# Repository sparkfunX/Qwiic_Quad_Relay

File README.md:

SparkX Qwiic Quad Relay
========================================

->  <-

[*SparkX Qwiic Quad Relay (SPX-15032)*](https://www.sparkfun.com/products/15032)
The Qwiic Quad Relay is a product designed for switching not one, but **four** high powered devices, from your Arduino or other low powered microcontroller using I<sup>2</sup>C. It's rocking four [relays](https://www.sparkfun.com/products/100) on its' PCB rated up to 5 Amps per channel at 250VAC. Each channel is sporting its own colored LED and silk for easy identification, and has screw terminals for easy connection. 

The board is made to integrate easily into the [Qwiic environment](https://www.sparkfun.com/qwiic) with Qwiic connectors on each side for easy daisy chaining. At the heart of the product is an ATtiny84 with its own I<sup>2</sup>C address awaiting for I<sup>2</sup>C commands that are designated to turn on and off individual channels or _all_ the channels at once! All of this is detailed nicely in provided example code, which also walks you through changing the boards single I<sup>2</sup>C address. There is a four pin header broken out for those of you not taking advantage of the Qwiic connector.

The onboard barrel jack is rated for wall warts in the range, 7-15V but there is a jumper on the underside in the case that your wall wart is 5V. Messing with such high voltage can be dangerous! We've included many safety precautions onto the PCB including, wide traces designed for high amperage, ground isolation between the relay and other circuitry, and a milled out area around the common pin of the relay.

Repository Contents
-------------------

* **/Firmware** - Latest firmware and examples. 
* **/Arduino Example** - Examples on how to use the product with buttons and switches, with hardware interrupts and without.
* **/Hardware** - Eagle design files (.brd, .sch)

License Information
-------------------

This product is _**open source**_! 

Please review the LICENSE.md file for license information. 

If you have any questions or concerns on licensing, please contact techsupport@sparkfun.com.

Please use, reuse, and modify these files as you see fit. Please maintain attribution to SparkFun Electronics and release under the same license.

Distributed as-is; no warranty is given.

- Your friends at SparkFun.

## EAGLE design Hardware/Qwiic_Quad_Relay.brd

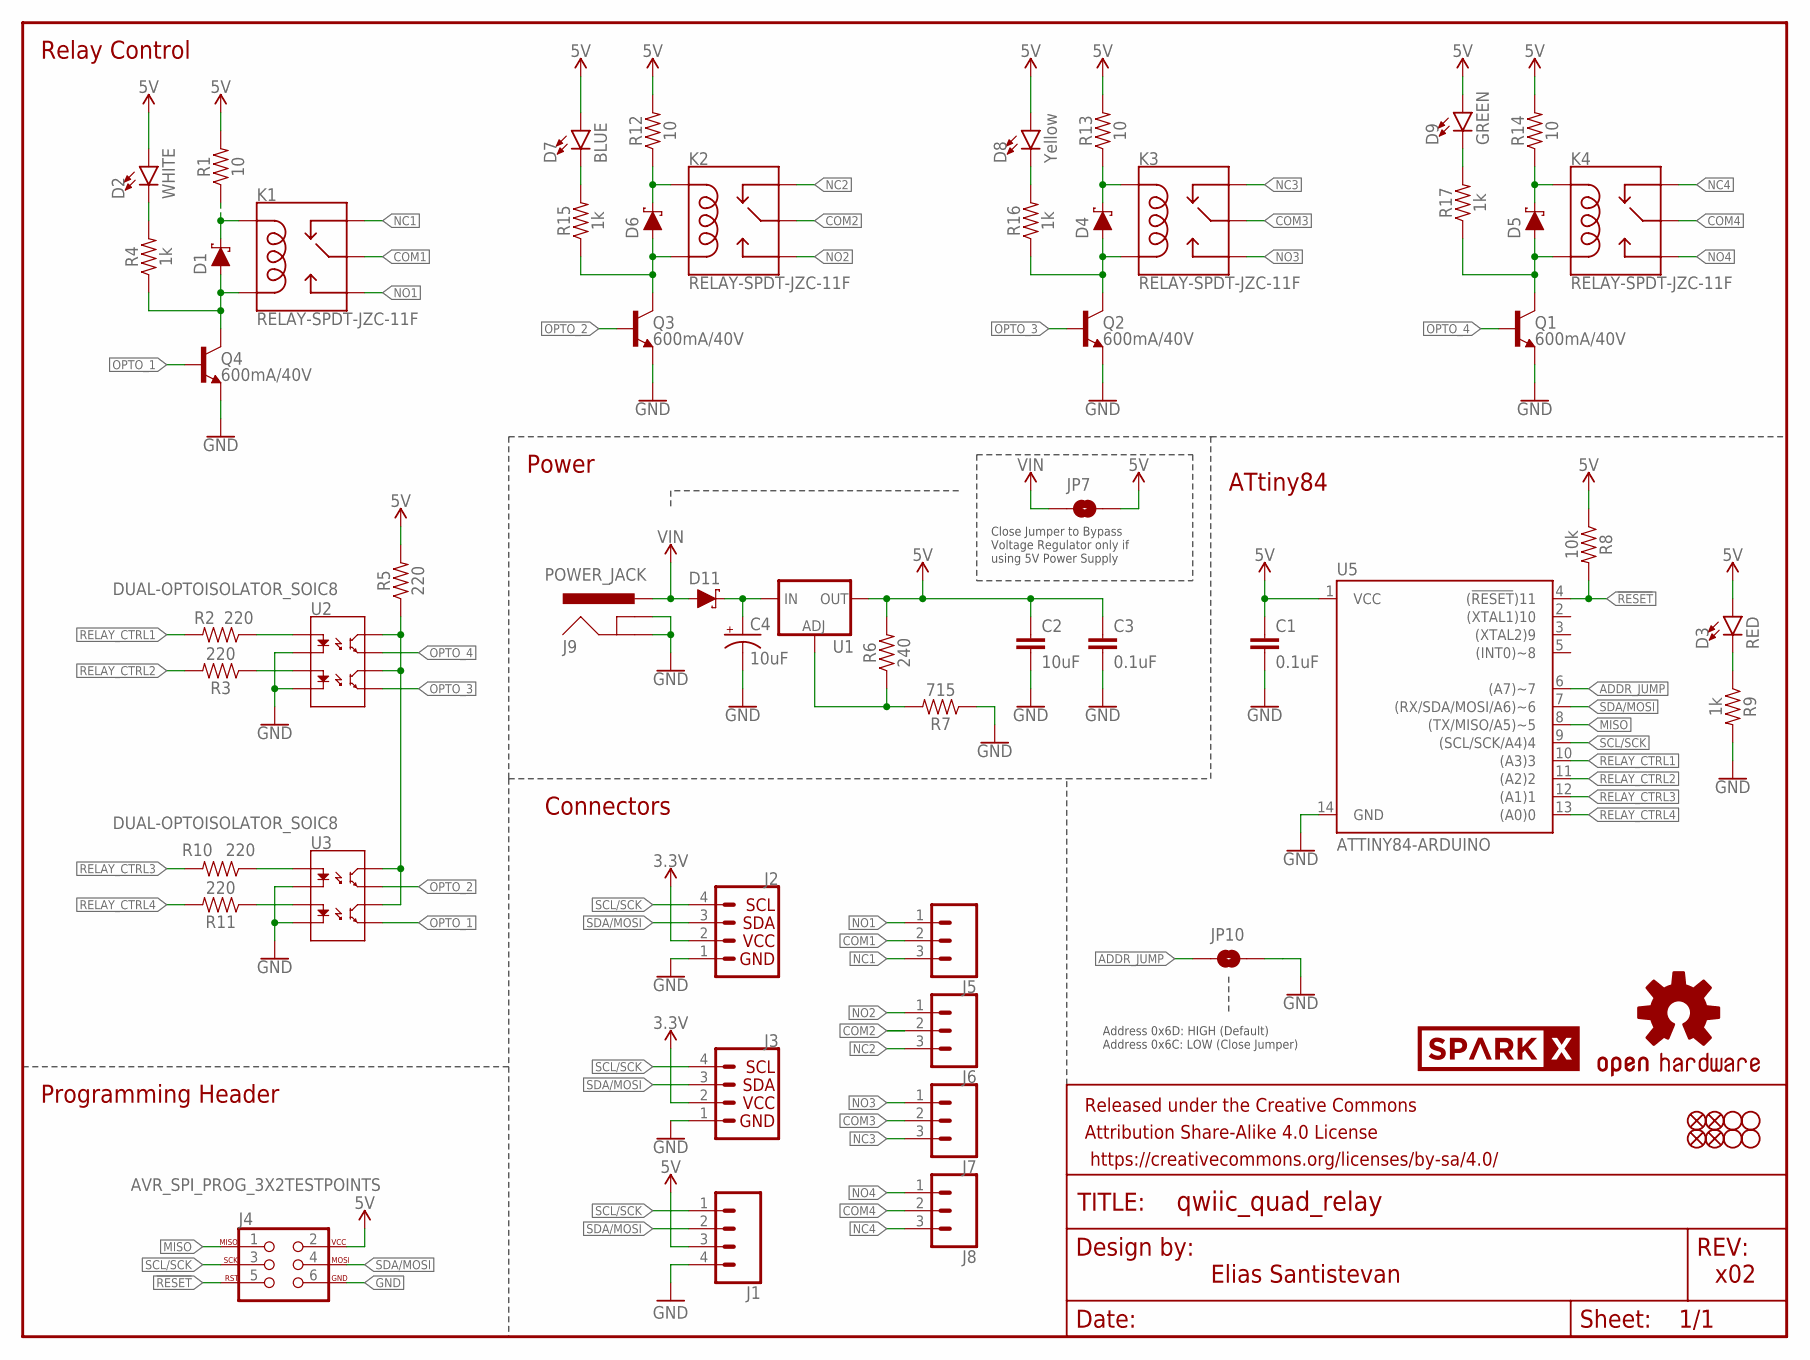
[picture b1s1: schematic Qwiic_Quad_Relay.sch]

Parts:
C1, C3: 0.1uF; 0603
C2: 10uF; 0603
C4: 10uF; EIA3528
D1, D4, D5, D6: 1A/23V/620mV; SOD-323
D2: WHITE; LED-0603
D3: RED; LED-0603
D7: BLUE; LED-0603
D8: Yellow; LED-0603
D9: GREEN; LED-0603
D11: 1A/40V/500mV; SMA-DIODE
FRAME1: FRAME-LETTER; CREATIVE_COMMONS
J1: CONN_041X04_NO_SILK; 1X04_NO_SILK
J2, J3: Qwiic Right Angle; 1X04_1MM_RA
J4: AVR_SPI_PROG_3X2TESTPOINTS; 2X3_TEST_POINTS
J5, J6, J7, J8: CONN_03-SCREW-5MM; SCREWTERMINAL-5MM-3
J9: POWER_JACK; POWER_JACK_PTH
JP1, JP3, JP4, JP5: STAND-OFF
JP2, JP6, JP8, JP9: FIDUCIAL1X2; FIDUCIAL-1X2
JP7, JP10: JUMPER-SMT_2_NO_SILK; SMT-JUMPER_2_NO_SILK
K1, K2, K3, K4: RELAY-SPDT-JZC-11F; RELAY-JZC
LOGO1: OSHW-LOGOS; OSHW-LOGO-S
Q1, Q2, Q3, Q4: 600mA/40V; SOT23-3
R1, R12, R13, R14: 10; 0603
R2, R3, R5, R10, R11: 220; 0603
R4, R9, R15, R16, R17: 1k; 0603
R6: 240; 0603
R7: 715; 0603
R8: 10k; 0603
U1: V_REG_LM1117SOT223; SOT223
U2, U3: DUAL-OPTOISOLATOR_SOIC8; SO08
U5: ATTINY84-ARDUINO; SO14
U$12: SPARKX-LOGO4; SPARKX-MEDIUM

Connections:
3.3V: J2.2, J3.2
5V: C1.1, C2.1, C3.1, D2.A, D3.A, D7.A, D8.A, D9.A, J1.3, J4.2, JP7.2, R1.2, R5.2, R6.2, R8.1, R12.2, R13.2, R14.2, U1.2 (OUT), U1.4 (OUT), U5.1 (VCC)
!RESET: J4.5, R8.2, U5.4 ((!RESET!)11)
ADDR_JUMP: JP10.1, U5.6 ((A7)~7)
COM1: J5.2, K1.4 (MAIN)
COM2: J6.2, K2.4 (MAIN)
COM3: J7.2, K3.4 (MAIN)
COM4: J8.2, K4.4 (MAIN)
GND: C1.2, C2.2, C3.2, C4.C (-), J1.4, J2.1, J3.1, J4.6, J9.GND, J9.GNDBREAK, JP10.2, Q1.2 (E), Q2.2 (E), Q3.2 (E), Q4.2 (E), R7.1, R9.2, U2.2 (C1), U2.4 (C2), U3.2 (C1), U3.4 (C2), U5.14 (GND)
MISO: J4.1, U5.8 ((TX/MISO/A5)~5)
unnamed: D6.C, K2.5 (COIL1), R12.1
unnamed: D1.A, K1.1 (COIL2), Q4.3 (C), R4.1
unnamed: R11.1, U3.3 (A2)
unnamed: C4.A (+), D11.C, U1.3 (IN)
unnamed: R10.1, U3.1 (A1)
unnamed: R5.1, U2.6 (CL2), U2.8 (CL1), U3.6 (CL2), U3.8 (CL1)
unnamed: D1.C, K1.5 (COIL1), R1.1
unnamed: D2.C, R4.2
unnamed: R2.1, U2.1 (A1)
unnamed: R3.1, U2.3 (A2)
unnamed: D6.A, K2.1 (COIL2), Q3.3 (C), R15.1
unnamed: D3.C, R9.1
unnamed: D4.C, K3.5 (COIL1), R13.1
unnamed: D4.A, K3.1 (COIL2), Q2.3 (C), R16.1
unnamed: D5.C, K4.5 (COIL1), R14.1
unnamed: D5.A, K4.1 (COIL2), Q1.3 (C), R17.1
unnamed: R6.1, R7.2, U1.1 (ADJ)
unnamed: D9.C, R17.2
unnamed: D8.C, R16.2
unnamed: D7.C, R15.2
NC1: J5.3, K1.2 (NC)
NC2: J6.3, K2.2 (NC)
NC3: J7.3, K3.2 (NC)
NC4: J8.3, K4.2 (NC)
NO1: J5.1, K1.3 (NO)
NO2: J6.1, K2.3 (NO)
NO3: J7.1, K3.3 (NO)
NO4: J8.1, K4.3 (NO)
OPTO_1: Q4.1 (B), U3.5 (EM2)
OPTO_2: Q3.1 (B), U3.7 (EM1)
OPTO_3: Q2.1 (B), U2.5 (EM2)
OPTO_4: Q1.1 (B), U2.7 (EM1)
RELAY_CTRL1: R2.2, U5.10 ((A3)3)
RELAY_CTRL2: R3.2, U5.11 ((A2)2)
RELAY_CTRL3: R10.2, U5.12 ((A1)1)
RELAY_CTRL4: R11.2, U5.13 ((A0)0)
SCL/SCK: J1.1, J2.4, J3.4, J4.3, U5.9 ((SCL/SCK/A4)4)
SDA/MOSI: J1.2, J2.3, J3.3, J4.4, U5.7 ((RX/SDA/MOSI/A6)~6)
VIN: D11.A, J9.PWR, JP7.1

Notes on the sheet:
Elias Santistevan
x02
Relay Control
Connectors
ATtiny84
Programming Header
Power
Close Jumper to Bypass Voltage Regulator only if using 5V Power Supply
Address 0x6D: HIGH (Default) Address 0x6C: LOW (Close Jumper)

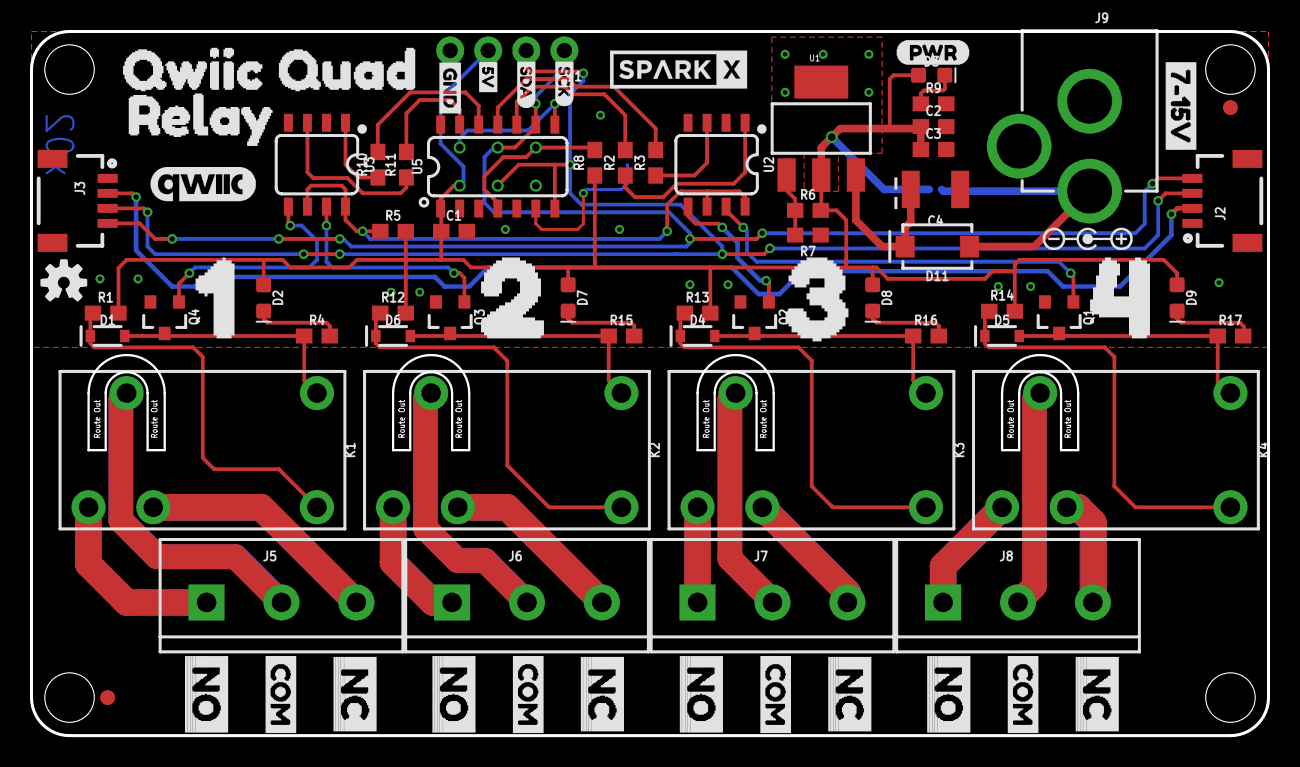
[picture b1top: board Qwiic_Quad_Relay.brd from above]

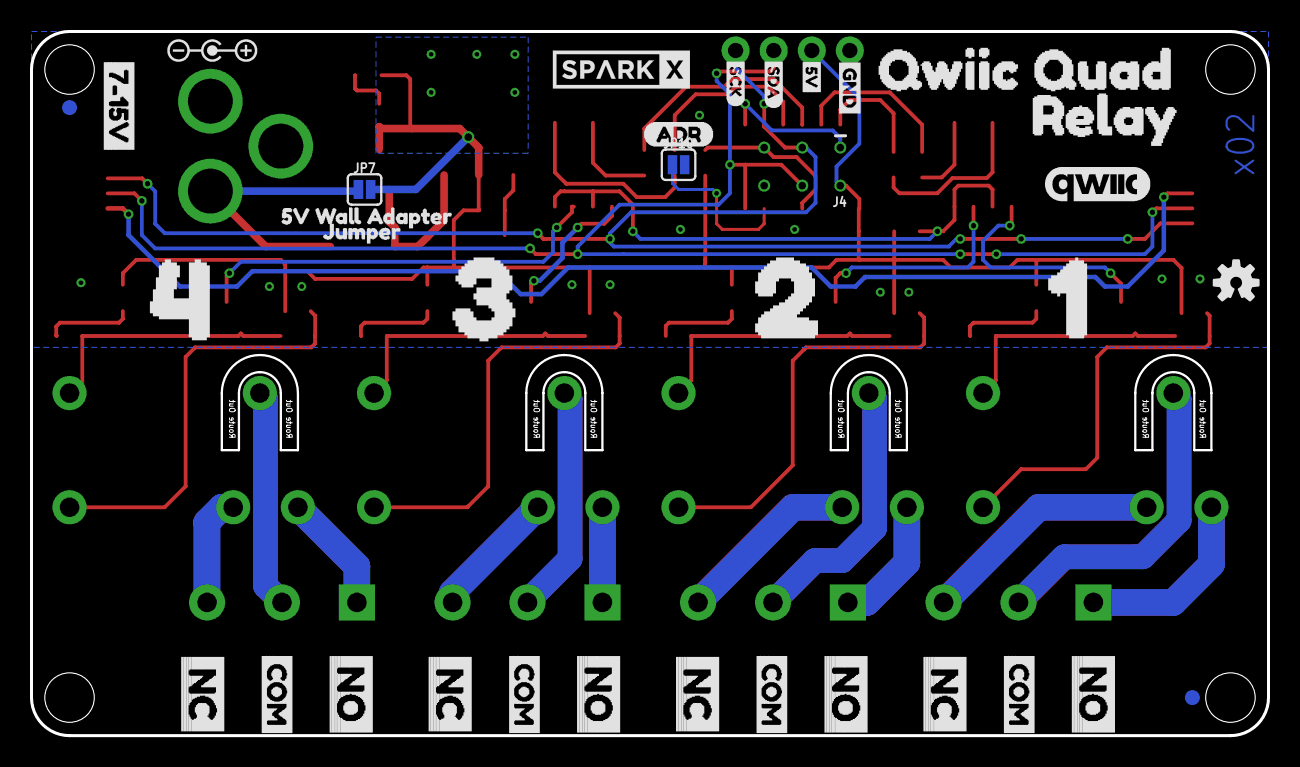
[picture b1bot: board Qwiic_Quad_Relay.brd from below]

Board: 2 copper layers, 82.5 x 47.0 mm, 121 parts (35 on the bottom side), 49 nets.

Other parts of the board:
U$1: PWR-()-04
U$2, U$40: 20
U$3, U$39: 10
U$4, U$41: 30
U$5, U$42: 40
U$6, U$43: QWIIC_QUAD_0
U$7, U$44: RELAY0
U$8, U$48: SCK-[)-03
U$9, U$45: GND-03
U$10, U$46: 5V0
U$11, U$47: SDA0
U$13: OSHW-LOGO-S
U$14: SPARKX-MEDIUM
U$15, U$18, U$21, U$24, U$27, U$30, U$33, U$36: NO0
U$16, U$19, U$22, U$25, U$28, U$31, U$34, U$37: COM0
U$17, U$20, U$23, U$26, U$29, U$32, U$35, U$38: NC0
U$49, U$53: 7#15V0
U$50: 5V_WALL_ADAPTER0
U$51, U$54: POLARITY_MARKING_CENTER_POSITIVE#JPG
U$52: JUMPER0
U$55, U$57: QWIIC#JPG
U$56: ADR-()-04

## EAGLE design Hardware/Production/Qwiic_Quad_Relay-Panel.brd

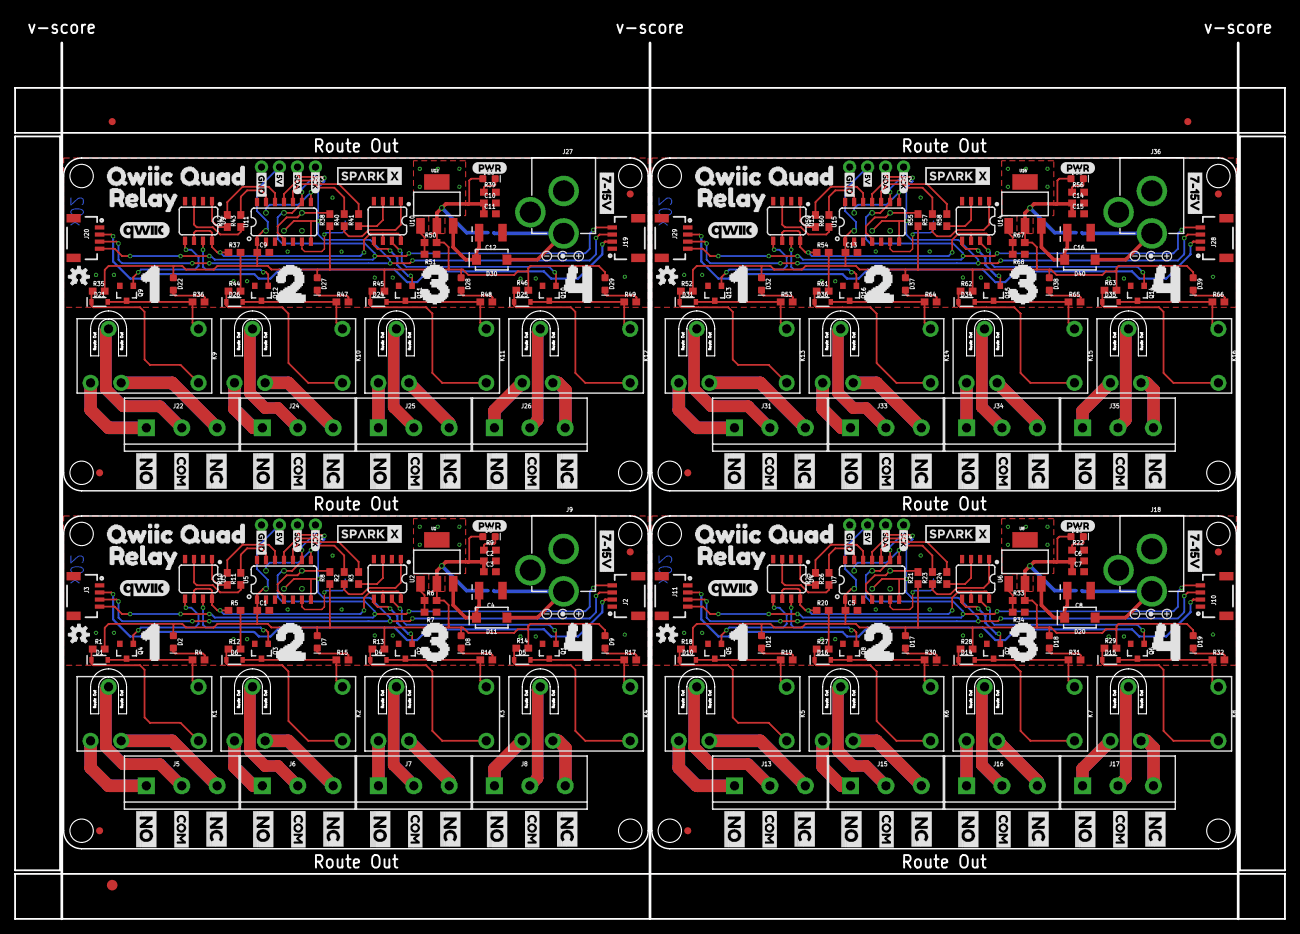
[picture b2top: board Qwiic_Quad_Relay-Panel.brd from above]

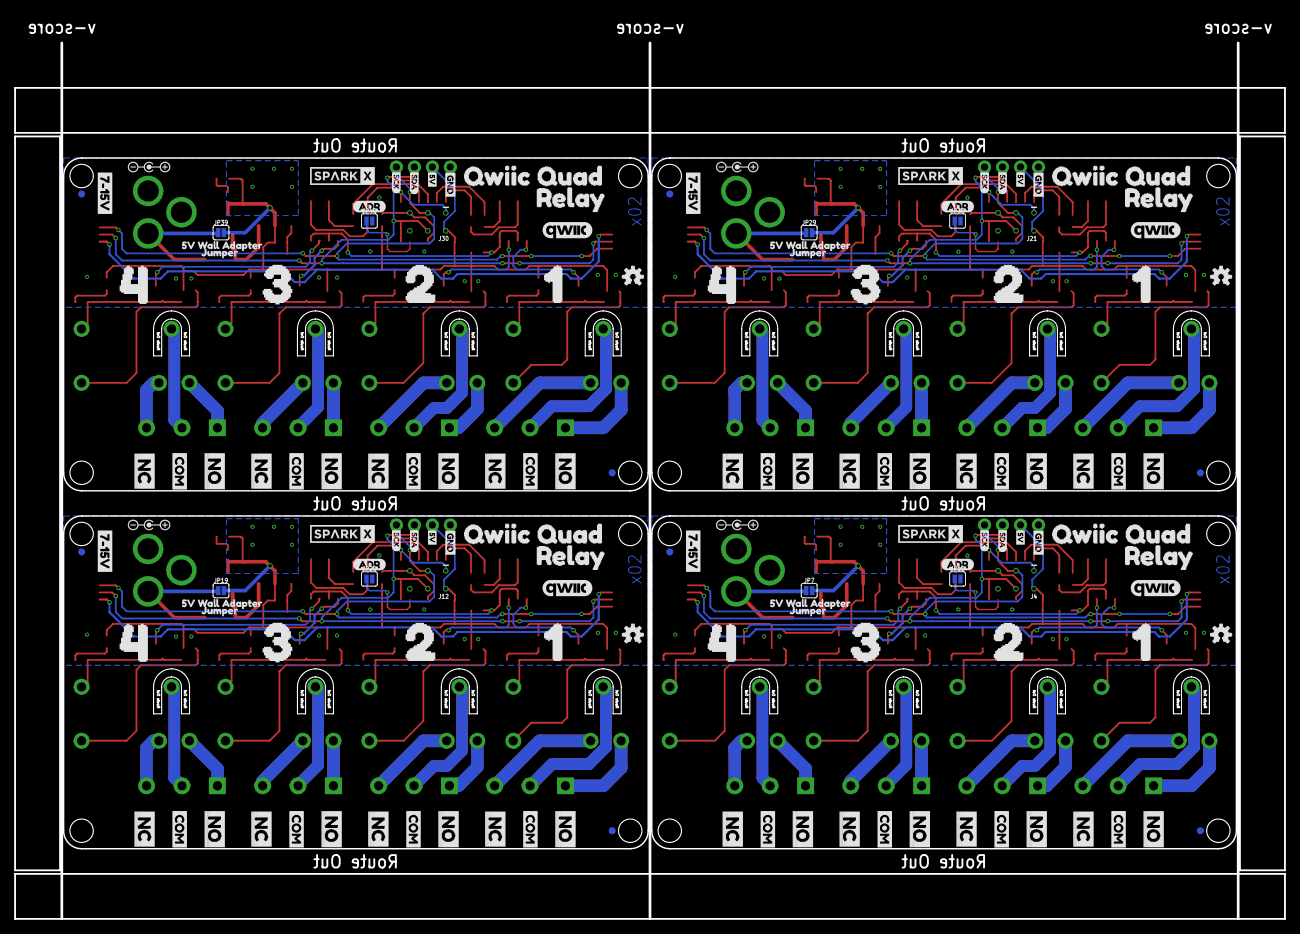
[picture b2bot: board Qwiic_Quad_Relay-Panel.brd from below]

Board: 2 copper layers, 179.2 x 127.6 mm, 483 parts (140 on the bottom side), 196 nets.

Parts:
C1, C3, C5, C7, C9, C11, C13, C15: 0.1uF; 0603
C2, C6, C10, C14: 10uF; 0603
C4, C8, C12, C16: 10uF; EIA3528
D1, D4, D5, D6, D10, D14, D15, D16, D21, D24, D25, D26, D31, D34, D35, D36: 1A/23V/620mV; SOD-323
D2, D12, D22, D32: WHITE; LED-0603
D3, D13, D23, D33: RED; LED-0603
D7, D17, D27, D37: BLUE; LED-0603
D8, D18, D28, D38: Yellow; LED-0603
D9, D19, D29, D39: GREEN; LED-0603
D11, D20, D30, D40: 1A/40V/500mV; SMA-DIODE
E$1, E$2: FIDUCIAL-1X2
E$3: FIDUCIAL-1.5X3
J1, J14, J23, J32: 1X04_NO_SILK
J2, J3, J10, J11, J19, J20, J28, J29: Qwiic Right Angle; 1X04_1MM_RA
J4, J12, J21, J30: AVR_SPI_PROG_3X2TESTPOINTS; 2X3_TEST_POINTS
J5, J6, J7, J8, J13, J15, J16, J17, J22, J24, J25, J26, J31, J33, J34, J35: SCREWTERMINAL-5MM-3
J9, J18, J27, J36: POWER_JACK; POWER_JACK_PTH
JP1, JP3, JP4, JP5, JP11, JP12, JP15, JP16, JP21, JP22, JP25, JP26, JP31, JP32, JP35, JP36: STAND-OFF
JP2, JP6, JP8, JP9, JP13, JP14, JP17, JP18, JP23, JP24, JP27, JP28, JP33, JP34, JP37, JP38: FIDUCIAL1X2; FIDUCIAL-1X2
JP7, JP10, JP19, JP20, JP29, JP30, JP39, JP40: JUMPER-SMT_2_NO_SILK; SMT-JUMPER_2_NO_SILK
K1, K2, K3, K4, K5, K6, K7, K8, K9, K10, K11, K12, K13, K14, K15, K16: RELAY-SPDT-JZC-11F; RELAY-JZC
LOGO1, LOGO2, LOGO3, LOGO4: OSHW-LOGOS; OSHW-LOGO-S
Q1, Q2, Q3, Q4, Q5, Q6, Q7, Q8, Q9, Q10, Q11, Q12, Q13, Q14, Q15, Q16: 600mA/40V; SOT23-3
R1, R12, R13, R14, R18, R27, R28, R29, R35, R44, R45, R46, R52, R61, R62, R63: 10; 0603
R2, R3, R5, R10, R11, R20, R23, R24, R25, R26, R37, R40, R41, R42, R43, R54, R57, R58, R59, R60: 220; 0603
R4, R9, R15, R16, R17, R19, R22, R30, R31, R32, R36, R39, R47, R48, R49, R53, R56, R64, R65, R66: 1k; 0603
R6, R33, R50, R67: 240; 0603
R7, R34, R51, R68: 715; 0603
R8, R21, R38, R55: 10k; 0603
U1, U8, U12, U16: SOT223
U2, U3, U4, U6, U9, U10, U13, U14: DUAL-OPTOISOLATOR_SOIC8; SO08
U5, U7, U11, U15: ATTINY84-ARDUINO; SO14
U$1, U$58, U$115, U$172: PWR-()-04
U$2, U$40, U$59, U$92, U$116, U$149, U$173, U$206: 20
U$3, U$39, U$60, U$91, U$117, U$148, U$174, U$205: 10
U$4, U$41, U$61, U$93, U$118, U$150, U$175, U$207: 30
U$5, U$42, U$62, U$94, U$119, U$151, U$176, U$208: 40
U$6, U$43, U$63, U$95, U$120, U$152, U$177, U$209: QWIIC_QUAD_0
U$7, U$44, U$64, U$96, U$121, U$153, U$178, U$210: RELAY0
U$8, U$48, U$99, U$106, U$156, U$163, U$213, U$220: SCK-[)-03
U$9, U$45, U$100, U$103, U$157, U$160, U$214, U$217: GND-03
U$10, U$46, U$101, U$104, U$158, U$161, U$215, U$218: 5V0
U$11, U$47, U$102, U$105, U$159, U$162, U$216, U$219: SDA0
U$12, U$65, U$122, U$179: SPARKX-LOGO4; SPARKX-MEDIUM
U$13, U$97, U$154, U$211: OSHW-LOGO-S
U$14, U$66, U$123, U$180: SPARKX-MEDIUM
U$15, U$18, U$21, U$24, U$27, U$30, U$33, U$36, U$67, U$70, U$73, U$76, U$79, U$82, U$85, U$88, U$124, U$127, U$130, U$133, U$136, U$139, U$142, U$145, U$181, U$184, U$187, U$190, U$193, U$196, U$199, U$202: NO0
U$16, U$19, U$22, U$25, U$28, U$31, U$34, U$37, U$68, U$71, U$74, U$77, U$80, U$83, U$86, U$89, U$125, U$128, U$131, U$134, U$137, U$140, U$143, U$146, U$182, U$185, U$188, U$191, U$194, U$197, U$200, U$203: COM0
U$17, U$20, U$23, U$26, U$29, U$32, U$35, U$38, U$69, U$72, U$75, U$78, U$81, U$84, U$87, U$90, U$126, U$129, U$132, U$135, U$138, U$141, U$144, U$147, U$183, U$186, U$189, U$192, U$195, U$198, U$201, U$204: NC0
U$49, U$53, U$98, U$108, U$155, U$165, U$212, U$222: 7#15V0
U$50, U$112, U$169, U$226: 5V_WALL_ADAPTER0
U$51, U$54, U$107, U$109, U$164, U$166, U$221, U$223: POLARITY_MARKING_CENTER_POSITIVE#JPG
U$52, U$113, U$170, U$227: JUMPER0
U$55, U$57, U$110, U$111, U$167, U$168, U$224, U$225: QWIIC#JPG
U$56, U$114, U$171, U$228: ADR-()-04

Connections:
3.3V: J2.2, J3.2
3.3V1: J10.2, J11.2
3.3V2: J19.2, J20.2
3.3V3: J28.2, J29.2
5V: C1.1, C2.1, C3.1, D2.A, D3.A, D7.A, D8.A, D9.A, J1.3, J4.2, JP7.2, R1.2, R5.2, R6.2, R8.1, R12.2, R13.2, R14.2, U1.2, U1.4, U5.1
5V1: C5.1, C6.1, C7.1, D12.A, D13.A, D17.A, D18.A, D19.A, J12.2, J14.3, JP19.2, R18.2, R20.2, R21.1, R27.2, R28.2, R29.2, R33.2, U7.1, U8.2, U8.4
5V2: C9.1, C10.1, C11.1, D22.A, D23.A, D27.A, D28.A, D29.A, J21.2, J23.3, JP29.2, R35.2, R37.2, R38.1, R44.2, R45.2, R46.2, R50.2, U11.1, U12.2, U12.4
5V3: C13.1, C14.1, C15.1, D32.A, D33.A, D37.A, D38.A, D39.A, J30.2, J32.3, JP39.2, R52.2, R54.2, R55.1, R61.2, R62.2, R63.2, R67.2, U15.1, U16.2, U16.4
!RESET: J4.5, R8.2, U5.4
!RESET1: J12.5, R21.2, U7.4
!RESET2: J21.5, R38.2, U11.4
!RESET3: J30.5, R55.2, U15.4
ADDR_JUMP: JP10.1, U5.6
ADDR_JUMP1: JP20.1, U7.6
ADDR_JUMP2: JP30.1, U11.6
ADDR_JUMP3: JP40.1, U15.6
COM1: J5.2, K1.4
COM2: J6.2, K2.4
COM3: J7.2, K3.4
COM4: J8.2, K4.4
COM5: J13.2, K5.4
COM6: J15.2, K6.4
COM7: J16.2, K7.4
COM8: J17.2, K8.4
COM9: J22.2, K9.4
COM10: J24.2, K10.4
COM11: J25.2, K11.4
COM12: J26.2, K12.4
COM13: J31.2, K13.4
COM14: J33.2, K14.4
COM15: J34.2, K15.4
COM16: J35.2, K16.4
GND: C1.2, C2.2, C3.2, C4.C, J1.4, J2.1, J3.1, J4.6, J9.GND, J9.GNDBREAK, JP10.2, Q1.2, Q2.2, Q3.2, Q4.2, R7.1, R9.2, U2.2, U2.4, U3.2, U3.4, U5.14
GND1: C5.2, C6.2, C7.2, C8.C, J10.1, J11.1, J12.6, J14.4, J18.GND, J18.GNDBREAK, JP20.2, Q5.2, Q6.2, Q7.2, Q8.2, R22.2, R34.1, U4.2, U4.4, U6.2, U6.4, U7.14
GND2: C9.2, C10.2, C11.2, C12.C, J19.1, J20.1, J21.6, J23.4, J27.GND, J27.GNDBREAK, JP30.2, Q9.2, Q10.2, Q11.2, Q12.2, R39.2, R51.1, U9.2, U9.4, U10.2, U10.4, U11.14
GND3: C13.2, C14.2, C15.2, C16.C, J28.1, J29.1, J30.6, J32.4, J36.GND, J36.GNDBREAK, JP40.2, Q13.2, Q14.2, Q15.2, Q16.2, R56.2, R68.1, U13.2, U13.4, U14.2, U14.4, U15.14
MISO: J4.1, U5.8
MISO1: J12.1, U7.8
MISO2: J21.1, U11.8
MISO3: J30.1, U15.8
unnamed: D6.C, K2.5, R12.1
unnamed: D1.A, K1.1, Q4.3, R4.1
unnamed: R11.1, U3.3
unnamed: C4.A, D11.C, U1.3
unnamed: R10.1, U3.1
unnamed: R5.1, U2.6, U2.8, U3.6, U3.8
unnamed: D1.C, K1.5, R1.1
unnamed: D2.C, R4.2
unnamed: R2.1, U2.1
unnamed: D10.A, K5.1, Q5.3, R19.1
unnamed: R3.1, U2.3
unnamed: D6.A, K2.1, Q3.3, R15.1
unnamed: D3.C, R9.1
unnamed: D4.C, K3.5, R13.1
unnamed: D4.A, K3.1, Q2.3, R16.1
unnamed: D5.C, K4.5, R14.1
unnamed: D5.A, K4.1, Q1.3, R17.1
unnamed: D10.C, K5.5, R18.1
unnamed: R6.1, R7.2, U1.1
unnamed: D9.C, R17.2
unnamed: D8.C, R16.2
unnamed: D7.C, R15.2
unnamed: D12.C, R19.2
unnamed: D13.C, R22.1
unnamed: R26.1, U4.3
unnamed: R25.1, U4.1
unnamed: R20.1, U4.6, U4.8, U6.6, U6.8
unnamed: R23.1, U6.1
unnamed: R24.1, U6.3
unnamed: D16.C, K6.5, R27.1
unnamed: D16.A, K6.1, Q8.3, R30.1
unnamed: D14.C, K7.5, R28.1
unnamed: D14.A, K7.1, Q7.3, R31.1
unnamed: D15.C, K8.5, R29.1
unnamed: D15.A, K8.1, Q6.3, R32.1
unnamed: D19.C, R32.2
unnamed: D18.C, R31.2
unnamed: D17.C, R30.2
unnamed: R33.1, R34.2, U8.1
unnamed: C8.A, D20.C, U8.3
unnamed: D21.A, K9.1, Q9.3, R36.1
unnamed: D21.C, K9.5, R35.1
unnamed: D22.C, R36.2
unnamed: D23.C, R39.1
unnamed: R43.1, U9.3
unnamed: R42.1, U9.1
unnamed: R37.1, U9.6, U9.8, U10.6, U10.8
unnamed: R40.1, U10.1
unnamed: R41.1, U10.3
unnamed: D26.C, K10.5, R44.1
unnamed: D26.A, K10.1, Q12.3, R47.1
unnamed: D24.C, K11.5, R45.1
unnamed: D24.A, K11.1, Q11.3, R48.1
unnamed: D25.C, K12.5, R46.1
unnamed: D25.A, K12.1, Q10.3, R49.1
unnamed: D29.C, R49.2
unnamed: D28.C, R48.2
unnamed: D27.C, R47.2
unnamed: R50.1, R51.2, U12.1
unnamed: C12.A, D30.C, U12.3
unnamed: D31.A, K13.1, Q13.3, R53.1
unnamed: D31.C, K13.5, R52.1
unnamed: D32.C, R53.2
unnamed: D33.C, R56.1
unnamed: R60.1, U13.3
unnamed: R59.1, U13.1
unnamed: R54.1, U13.6, U13.8, U14.6, U14.8
unnamed: R57.1, U14.1
unnamed: R58.1, U14.3
unnamed: D36.C, K14.5, R61.1
unnamed: D36.A, K14.1, Q16.3, R64.1
unnamed: D34.C, K15.5, R62.1
unnamed: D34.A, K15.1, Q15.3, R65.1
unnamed: D35.C, K16.5, R63.1
unnamed: D35.A, K16.1, Q14.3, R66.1
unnamed: D39.C, R66.2
unnamed: D38.C, R65.2
unnamed: D37.C, R64.2
unnamed: R67.1, R68.2, U16.1
unnamed: C16.A, D40.C, U16.3
NC1: J5.3, K1.2
NC2: J6.3, K2.2
NC3: J7.3, K3.2
NC4: J8.3, K4.2
NC5: J13.3, K5.2
NC6: J15.3, K6.2
NC7: J16.3, K7.2
NC8: J17.3, K8.2
NC9: J22.3, K9.2
NC10: J24.3, K10.2
NC11: J25.3, K11.2
NC12: J26.3, K12.2
NC13: J31.3, K13.2
NC14: J33.3, K14.2
NC15: J34.3, K15.2
NC16: J35.3, K16.2
NO1: J5.1, K1.3
NO2: J6.1, K2.3
NO3: J7.1, K3.3
NO4: J8.1, K4.3
NO5: J13.1, K5.3
NO6: J15.1, K6.3
NO7: J16.1, K7.3
NO8: J17.1, K8.3
NO9: J22.1, K9.3
NO10: J24.1, K10.3
NO11: J25.1, K11.3
NO12: J26.1, K12.3
NO13: J31.1, K13.3
NO14: J33.1, K14.3
NO15: J34.1, K15.3
NO16: J35.1, K16.3
OPTO_1: Q4.1, U3.5
OPTO_2: Q3.1, U3.7
OPTO_3: Q2.1, U2.5
OPTO_4: Q1.1, U2.7
OPTO_5: Q5.1, U4.5
OPTO_6: Q8.1, U4.7
OPTO_7: Q7.1, U6.5
OPTO_8: Q6.1, U6.7
OPTO_9: Q9.1, U9.5
OPTO_10: Q12.1, U9.7
OPTO_11: Q11.1, U10.5
OPTO_12: Q10.1, U10.7
OPTO_13: Q13.1, U13.5
OPTO_14: Q16.1, U13.7
OPTO_15: Q15.1, U14.5
OPTO_16: Q14.1, U14.7
RELAY_CTRL1: R2.2, U5.10
RELAY_CTRL2: R3.2, U5.11
RELAY_CTRL3: R10.2, U5.12
RELAY_CTRL4: R11.2, U5.13
RELAY_CTRL5: R23.2, U7.10
RELAY_CTRL6: R24.2, U7.11
RELAY_CTRL7: R25.2, U7.12
RELAY_CTRL8: R26.2, U7.13
RELAY_CTRL9: R40.2, U11.10
RELAY_CTRL10: R41.2, U11.11
RELAY_CTRL11: R42.2, U11.12
RELAY_CTRL12: R43.2, U11.13
RELAY_CTRL13: R57.2, U15.10
RELAY_CTRL14: R58.2, U15.11
RELAY_CTRL15: R59.2, U15.12
RELAY_CTRL16: R60.2, U15.13
SCL/SCK: J1.1, J2.4, J3.4, J4.3, U5.9
SCL/SCK1: J10.4, J11.4, J12.3, J14.1, U7.9
SCL/SCK2: J19.4, J20.4, J21.3, J23.1, U11.9
SCL/SCK3: J28.4, J29.4, J30.3, J32.1, U15.9
SDA/MOSI: J1.2, J2.3, J3.3, J4.4, U5.7
SDA/MOSI1: J10.3, J11.3, J12.4, J14.2, U7.7
SDA/MOSI2: J19.3, J20.3, J21.4, J23.2, U11.7
SDA/MOSI3: J28.3, J29.3, J30.4, J32.2, U15.7
VIN: D11.A, J9.PWR, JP7.1
VIN1: D20.A, J18.PWR, JP19.1
VIN2: D30.A, J27.PWR, JP29.1
VIN3: D40.A, J36.PWR, JP39.1

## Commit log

2018-09-18 Ready for review
2018-09-21 Silk, diode, different LEDs, jumper, rounded route out
    I changed to better consistency of label size, a center positive label for the barrel jack, and added the new qwiic label to our new standard. Used different color LEDs so that a person could identif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
2018-09-21 Changed internal route out to milling, also production files.
2018-10-04 Example Code, Firmware, Changes to board
    Example Code is not done, firmware as well, unless I want to add a bit more to toggle all channels to opposite states. Production Files have been added. Induction resistor has been changed to a 100 O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
2018-10-12 Updates to board file, example code, and firmware for release!
2018-10-16 Version x02
    Changes:
    Added thermal polygon around and underneath the voltage regulator.
    Changed LED resistor values to 1k because they were too bright.
    Added address jumper.
    Modified relay pins
    Changed Firmware to add second I2C address
2018-10-16 Production Files Updated
2018-10-19 Picture for README

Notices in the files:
parts and their libraries:
SparkFun-Capacitors: Licensing: Creative Commons ShareAlike 4.0 International - https://creativecommons.org/licenses/by-sa/4.0
SparkFun-Aesthetics: Released under the Creative Commons Attribution Share-Alike 4.0 License
SparkFun-Aesthetics: https://creativecommons.org/licenses/by-sa/4.0
